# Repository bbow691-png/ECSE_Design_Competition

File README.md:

🥁 ESP32 & Godot Rhythm Game

An open-source, hybrid rhythm game project combining custom ESP32 hardware (piezo drum pads over I2S) with a Godot 4.x game engine frontend. Hit your physical drum kit, stream analog transients via high-speed ADC sampling, and watch the notes fall in sync on your screen!

🛠️ Project Structure
├── src/                      # C++ PlatformIO firmware for the ESP32
├── godot/ecse-design/        # Godot 4.x Game Engine Project
│   ├── scenes/game_scene/    # Gameplay levels, lanes, and UI
│   ├── scripts/              # SongManager, PiezoInput, and Conductor logic
│   └── songs/                # JSON-based custom beatmaps & audio
└── run_instructions.md       # Detailed local setup guide
⚡ Part 1: Hardware Setup & ESP32 Firmware

The ESP32 uses built-in I2S ADC sampling at 20kHz to capture percussive transients from up to 4 piezo drum pads simultaneously, translating analog strikes into MIDI velocity data over USB Serial.

Prerequisites
VS Code with the PlatformIO extension installed
Flashing the ESP32
Open VS Code and use File > Open Folder to select the root folder containing your platformio.ini file.
Wait for PlatformIO to automatically download the required ESP32 toolchains and Arduino frameworks.
Plug your ESP32 into your computer via USB.
Click the Upload and Monitor button on the bottom status bar (or run PlatformIO: Upload and Monitor).
Tap your piezo drums — you should see live symbols popping up in the terminal.
Close the terminal and run stream_audio.py. This will result in meaningful text appearing in your terminal.
🎮 Part 2: Godot Game Engine Setup

The Godot frontend listens to incoming serial/network streams, handles lane input, and manages synchronized audio tracking alongside JSON-driven beatmaps.

Prerequisites
Godot Engine 4.x
Running the Project
Launch Godot Engine and click Import on the Project Manager screen.
Navigate into the repository folder, select the godot/ecse-design/ sub-folder, and select the project.godot file.
Once the editor loads your project, click the Play button (or press F5) in the top right corner.
🎵 Adding Custom Songs & Beatmaps

Songs are loaded dynamically via JSON files processed globally by the SongManager singleton.

To add a new song:

Create a folder inside res://songs/your_song_name/.
Add your audio file and a beatmap.json file structured like this:
json
{
  "title": "Your Song Title",
  "bpm": 120,
  "notes": [
    { "time": 2.0, "pad": 0 },
    { "time": 3.0, "pad": 1 },
    { "time": 4.0, "pad": 2 },
    { "time": 5.0, "pad": 3 }
  ]
}
Trigger the song in your scene script:
gdscript
SongManager.load_and_play_song("res://songs/your_song_name")
📄 License

This project is open-source and available for educational and personal use.

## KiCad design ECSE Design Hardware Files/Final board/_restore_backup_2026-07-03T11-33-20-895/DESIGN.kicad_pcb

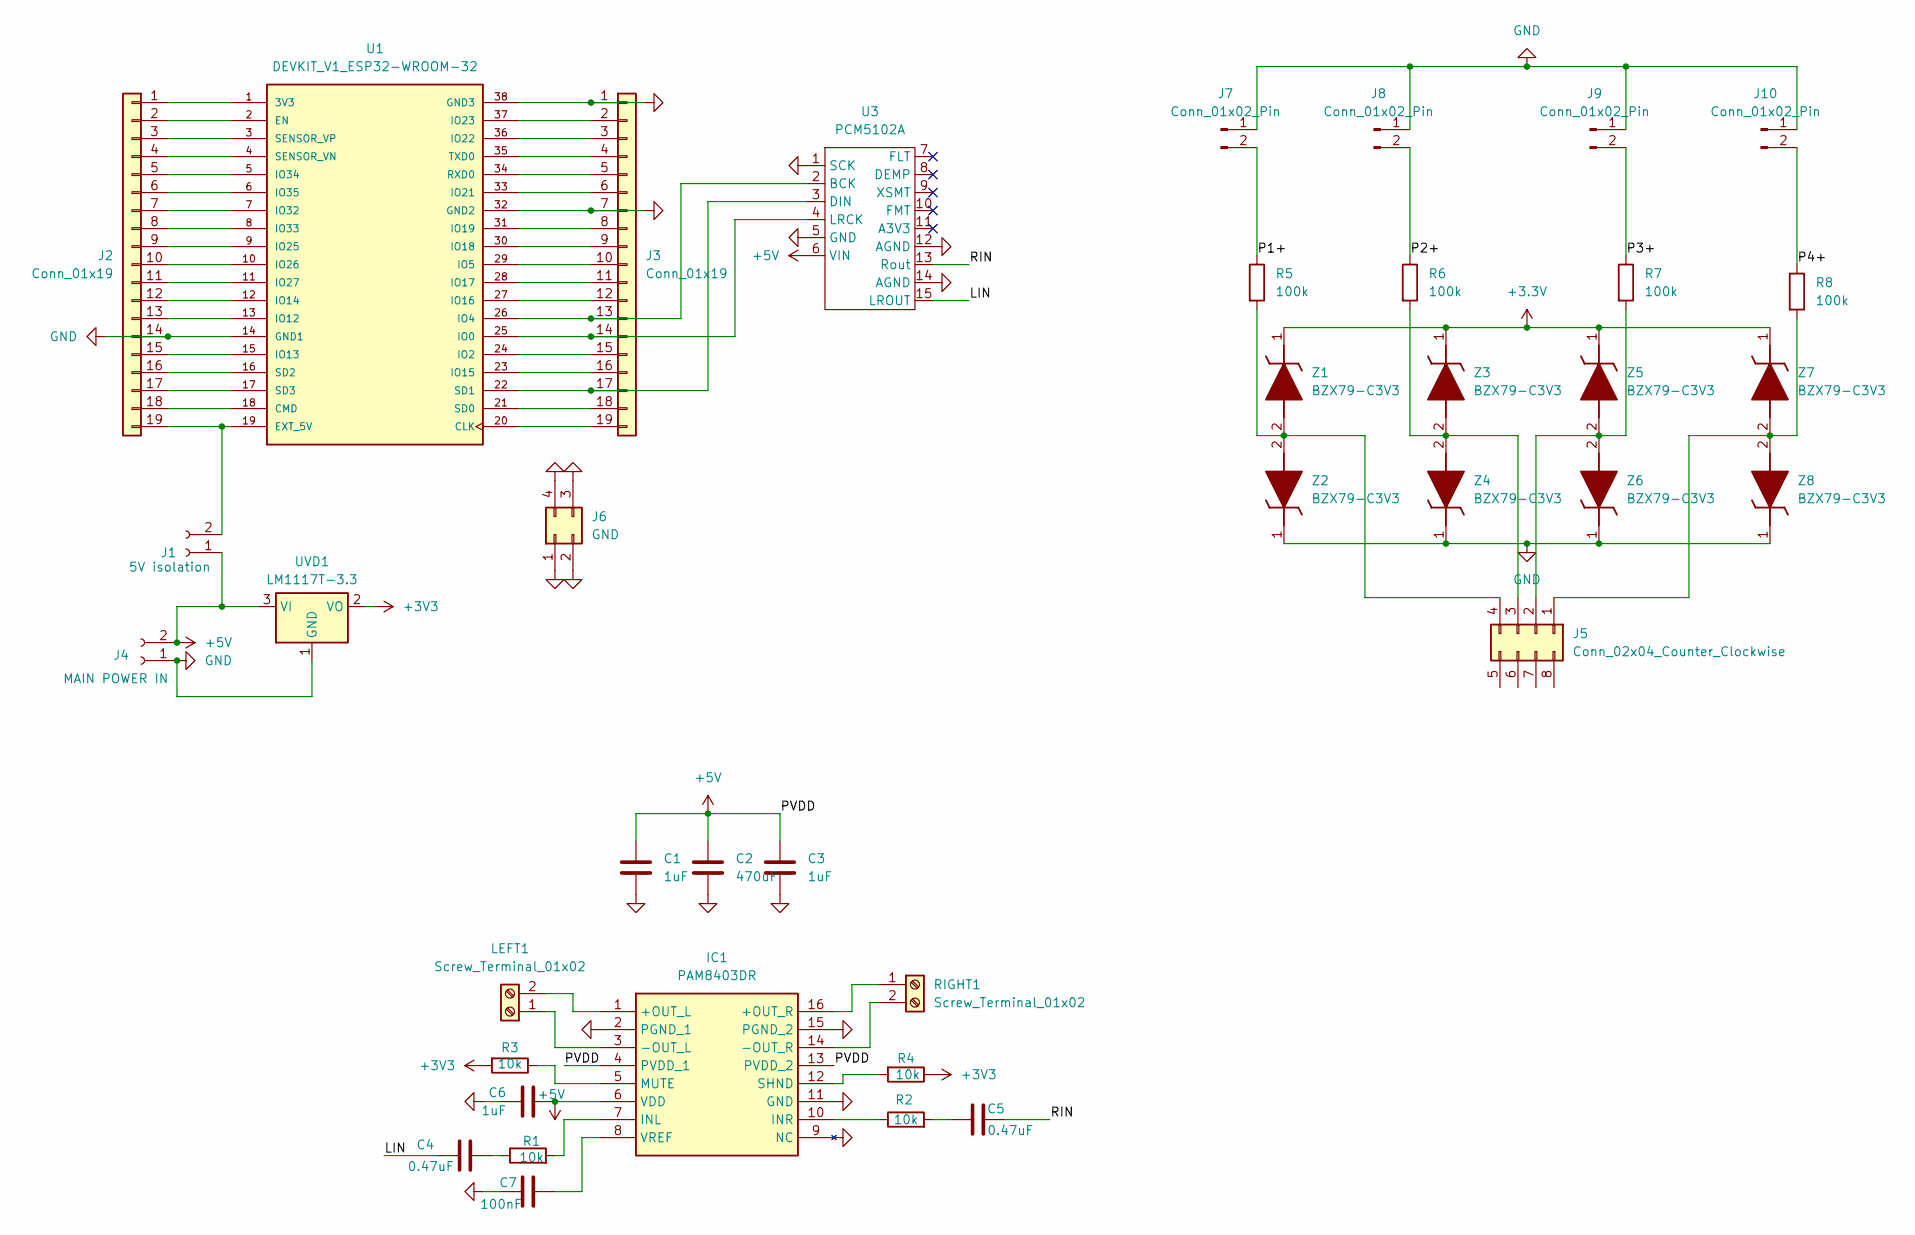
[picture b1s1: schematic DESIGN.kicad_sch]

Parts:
C1, C3, C6: 1uF; C_0805_2012Metric_Pad1.18x1.45mm_HandSolder
C2: 470uF; CP_Radial_D10.0mm_P5.00mm
C4: 0.47uF; C_0805_2012Metric_Pad1.18x1.45mm_HandSolder
C5: 0.47uF
C7: 100nF; C_0805_2012Metric_Pad1.18x1.45mm_HandSolder
IC1: PAM8403DR; SOIC127P600X126-16N; Manufacturer_Part_Number PAM8403DR; Mouser Part Number 621-PAM8403DR
J1: 5V isolation; PinHeader_1x02_P2.54mm_Vertical
J2, J3: Conn_01x19; PinHeader_1x19_P2.54mm_Vertical
J4: MAIN POWER IN; Power ECSE Design
J5: Conn_02x04_Counter_Clockwise; PinHeader_2x04_P2.54mm_Vertical
J6: GND
J7, J8, J9, J10: Conn_01x02_Pin; PinHeader_1x02_P2.54mm_Vertical
LEFT1: Screw_Terminal_01x02; TerminalBlock_MaiXu_MX126-5.0-02P_1x02_P5.00mm
R1, R2, R3, R4: 10k; R_0805_2012Metric_Pad1.20x1.40mm_HandSolder
R5, R6, R7, R8: 100k; R_0805_2012Metric_Pad1.20x1.40mm_HandSolder
RIGHT1: Screw_Terminal_01x02; TerminalBlock_MaiXu_MX126-5.0-02P_1x02_P5.00mm
U1: DEVKIT_V1_ESP32-WROOM-32; MODULE_DEVKIT_V1_ESP32-WROOM-32; PARTREV N/A
U3: PCM5102A
UVD1: LM1117T-3.3; TO-220-3_Vertical
Z1, Z2, Z3, Z4, Z5, Z6, Z7, Z8: BZX79-C3V3; DIOAD1165W56L425D185; Manufacturer_Part_Number BZX79-C3V3; Mouser Part Number N/A

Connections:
+3.3V: Z1.1 (K), Z3.1 (K), Z5.1 (K), Z7.1 (K)
+3V3: R3.2, R4.1, UVD1.2 (VO)
+5V: C1.1, C2.1, C3.1, C6.2, IC1.4 (PVDD_1), IC1.6 (VDD), IC1.13 (PVDD_2), J1.1, J4.2, U3.6 (VIN), UVD1.3 (VI)
/LIN: C4.1, U3.15 (LROUT)
/P1+: J7.2, R5.1
/P2+: J8.2, R6.1
/P3+: J9.2, R7.1
/P4+: J10.2, R8.1
/RIN: C5.2, U3.13 (Rout)
GND: C1.2, C2.2, C3.2, C6.1, C7.1, IC1.2 (PGND_1), IC1.9 (NC), IC1.11 (GND), IC1.15 (PGND_2), J2.14, J3.1, J3.7, J4.1, J6.1, J6.2, J6.3, J6.4, J7.1, J8.1, J9.1, J10.1, U1.14 (GND1), U1.32 (GND2), U1.38 (GND3), U3.1 (SCK), U3.5 (GND), U3.12 (AGND), U3.14 (AGND), UVD1.1 (GND), Z2.1 (K), Z4.1 (K), Z6.1 (K), Z8.1 (K)
unnamed: C4.2, R1.1
unnamed: C5.1, R2.2
unnamed: IC1.1 (+OUT_L), LEFT1.2
unnamed: IC1.16 (+OUT_R), RIGHT1.1
unnamed: IC1.3 (-OUT_L), LEFT1.1
unnamed: IC1.14 (-OUT_R), RIGHT1.2
unnamed: IC1.7 (INL), R1.2
unnamed: IC1.10 (INR), R2.1
unnamed: IC1.5 (MUTE), R3.1
unnamed: IC1.12 (SHND), R4.2
unnamed: C7.2, IC1.8 (VREF)
unnamed: J1.2, J2.19, U1.19 (EXT_5V)
unnamed: J2.1, U1.1 (3V3)
unnamed: J2.2, U1.2 (EN)
unnamed: J2.3, U1.3 (SENSOR_VP)
unnamed: J2.4, U1.4 (SENSOR_VN)
unnamed: J2.5, U1.5 (IO34)
unnamed: J2.6, U1.6 (IO35)
unnamed: J2.7, U1.7 (IO32)
unnamed: J2.8, U1.8 (IO33)
unnamed: J2.9, U1.9 (IO25)
unnamed: J2.10, U1.10 (IO26)
unnamed: J2.11, U1.11 (IO27)
unnamed: J2.12, U1.12 (IO14)
unnamed: J2.13, U1.13 (IO12)
unnamed: J2.15, U1.15 (IO13)
unnamed: J2.16, U1.16 (SD2)
unnamed: J2.17, U1.17 (SD3)
unnamed: J2.18, U1.18 (CMD)
unnamed: J3.2, U1.37 (IO23)
unnamed: J3.3, U1.36 (IO22)
unnamed: J3.4, U1.35 (TXD0)
unnamed: J3.5, U1.34 (RXD0)
unnamed: J3.6, U1.33 (IO21)
unnamed: J3.8, U1.31 (IO19)
unnamed: J3.9, U1.30 (IO18)
unnamed: J3.10, U1.29 (IO5)
unnamed: J3.11, U1.28 (IO17)
unnamed: J3.12, U1.27 (IO16)
unnamed: J3.13, U1.26 (IO4), U3.2 (BCK)
unnamed: J3.14, U1.25 (IO0), U3.4 (LRCK)
unnamed: J3.15, U1.24 (IO2)
unnamed: J3.16, U1.23 (IO15)
unnamed: J3.17, U1.22 (SD1), U3.3 (DIN)
unnamed: J3.18, U1.21 (SD0)
unnamed: J3.19, U1.20 (CLK)
unnamed 56: J5.1, R8.2, Z7.2 (A), Z8.2 (A); also elsewhere on the board
unnamed 57: J5.2, R7.2, Z5.2 (A), Z6.2 (A); also elsewhere on the board
unnamed 58: J5.3, R6.2, Z3.2 (A), Z4.2 (A); also elsewhere on the board
unnamed 59: J5.4, R5.2, Z1.2 (A), Z2.2 (A); also elsewhere on the board

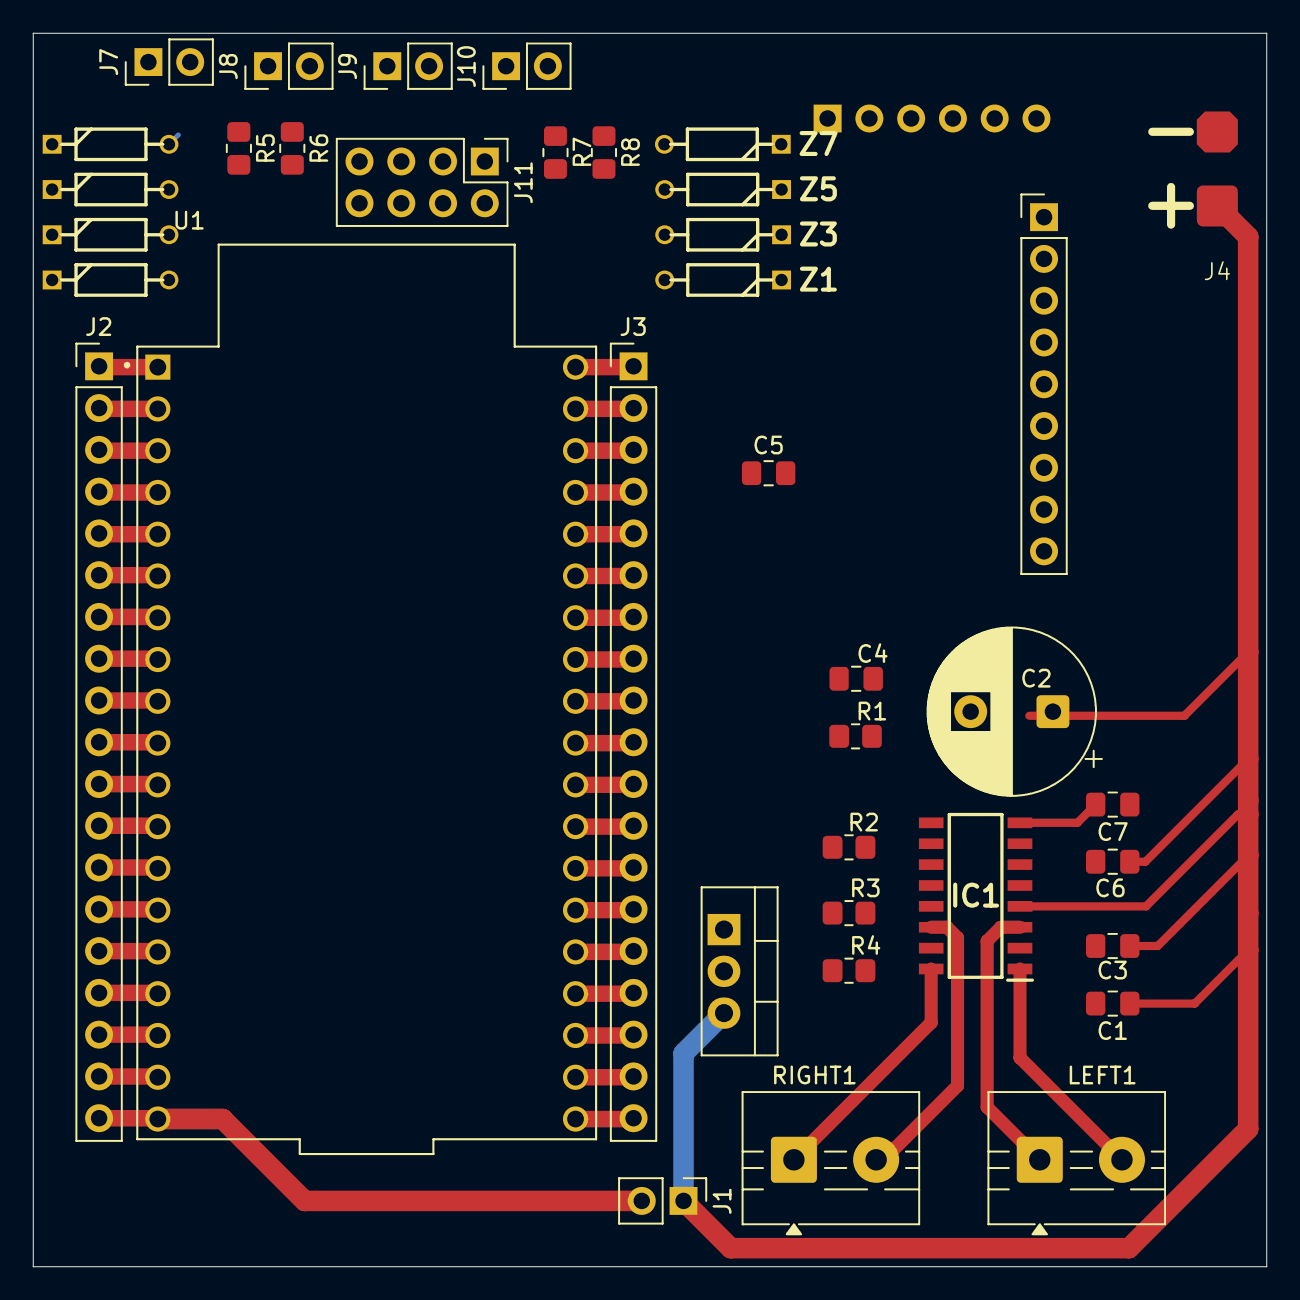
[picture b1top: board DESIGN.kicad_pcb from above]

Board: 2 copper layers, 75.0 x 75.0 mm, 38 parts (0 on the bottom side), 60 nets.

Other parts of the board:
J11: Conn_02x04_Odd_Even; PinHeader_2x04_P2.54mm_Vertical

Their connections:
unnamed 56: J11.1; also elsewhere on the board
unnamed 57: J11.3; also elsewhere on the board
unnamed 58: J11.5; also elsewhere on the board
unnamed 59: J11.7; also elsewhere on the board
